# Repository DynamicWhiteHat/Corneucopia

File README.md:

# Corneucopia
A Corne based custom low-profile keyboard 

---

Corneucopia is a 42-key low profile wireless keyboard that runs on ZMK firmware. Featuring 2 OLED displays and powered by a Supermini NRF52840, this keyboard is meant to last as your daily driver. 

# Features
- 42 keys
- Per key RGB
- 2x Nice!View
- 2x Supermini NRF52840 (Nice!Nano clone)
- Hotswap sockets
- Low profile choc switches

# Why I Made This
I was initally wary of split or ergonomic keyboards as I thought they looked bad. However, while I was designing my own regular keyboard, I came across split ergo keyboards online that caught my eye, especially [this](https://www.etsy.com/listing/1337908749/ready-to-use-crkbd-corne-keyboard-v301) one. I slowly came to appreciate the look and layout of Corne keyboards, so I decided to make one. This project was a test of my PCB and CAD design skills, as well as a test of my ability to learn new things (ergogen). Overall, I think this came out very well.

# Pictures
## CAD

## PCB

## Schematic

# BOM
Note: 
- Typeractive was sometimes cheaper than AliExpress, thus some parts were sourced from them instead.
- Keycaps will be 3D printed

| Part                | Quantity      | Price   | Link                                                                                                                                                                                                                                                                                                                                                                                                                                                                                                                                      |
|---------------------|---------------|---------|-------------------------------------------------------------------------------------------------------------------------------------------------------------------------------------------------------------------------------------------------------------------------------------------------------------------------------------------------------------------------------------------------------------------------------------------------------------------------------------------------------------------------------------------|
| Kailh Hotswaps      |            70 |   $4.30 | https://www.aliexpress.us/item/3256807045726008.html?spm=a2g0o.productlist.main.6.626d50b5izCjus&algo_pvid=53812c83-dfd7-4376-8f8e-c34f3db6f02e&algo_exp_id=53812c83-dfd7-4376-8f8e-c34f3db6f02e-5&pdp_ext_f=%7B%22order%22%3A%22708%22%2C%22eval%22%3A%221%22%7D&pdp_npi=4%40dis%21USD%218.49%213.91%21%21%2160.92%2128.02%21%402103244b17542247069335737e297b%2112000039893759775%21sea%21US%216238534509%21X&curPageLogUid=VnLZ55itI6I3&utparam-url=scene%3Asearch%7Cquery_from%3A                                                     |
| Choc Switches       | 1 Pack of 70  |  $33.29 | https://www.amazon.com/Mechanical-Keyboard-switches-Chocolate-Pro-70Pcs/dp/B0DDCBL4KJ/ref=sr_1_3?crid=32V01OVDG0FH6&dib=eyJ2IjoiMSJ9.fxBe5Z4GEMZJbyuF_eaa4d6xI5EsW9uxe8cNgFLYw9cyOJJo5evMOuEAVRduMsGcHGBmw3MapZWf-BWJmWWDj5YY16v4twxpLxE8v6OxY93s_vstH-ICQffONlwd1cMobpg0_pCQesoQGqMTI_Z54wqwIzkdmZYqtPJTFfRFv11-gn-8LCyKCC6uGZ-SY1KXOGvvkI4U1F0dRwDqiQvPOQNUksX0ZSc9md0I7E6eDgI.r2LF0urYCczODaFRTe6UtlDuNLtg5oKRx1Cg0aavuK4&dib_tag=se&keywords=kailh%2Bchoc%2Bred%2Bpro&qid=1754222624&sprefix=choc%2Bpro%2Bred%2Caps%2C268&sr=8-3&th=1 |
| 1N4148 Diodes       | 1 Pack of 100 |   $1.40 | https://www.aliexpress.us/item/3256806137153769.html?spm=a2g0o.productlist.main.1.145669f2x3hJ9l&algo_pvid=26801ca0-fa57-43dc-bef8-9addec3b9d2b&algo_exp_id=26801ca0-fa57-43dc-bef8-9addec3b9d2b-0&pdp_ext_f=%7B%22order%22%3A%22395%22%2C%22eval%22%3A%221%22%7D&pdp_npi=4%40dis%21USD%211.40%211.40%21%21%2110.01%2110.01%21%40210312d517540153367636770eae10%2112000041342157154%21sea%21US%216238534509%21X&curPageLogUid=Ny6g9i4BYw4L&utparam-url=scene%3Asearch%7Cquery_from%3A                                                     |
| Nice!View           |             2 |  $40.00 | https://typeractive.xyz/products/nice-view                                                                                                                                                                                                                                                                                                                                                                                                                                                                                                |
| Supermini NRF52840  |             2 |   $5.77 | https://www.aliexpress.us/item/3256807552571798.html?gatewayAdapt=glo2usa4itemAdapt#nav-description                                                                                                                                                                                                                                                                                                                                                                                                                                       |
| Reset Button        | 1 Pack of 2   |   $1.50 | https://typeractive.xyz/products/reset-button                                                                                                                                                                                                                                                                                                                                                                                                                                                                                             |
| Power Switch        | 1 Pack of 2   |   $1.50 | https://typeractive.xyz/products/power-switch                                                                                                                                                                                                                                                                                                                                                                                                                                                                                             |
| Mill Max            |             2 |     $13 | https://typeractive.xyz/products/machine-sockets-and-pins                                                                                                                                                                                                                                                                                                                                                                                                                                                                                 |
| 110 mAh Battery     |             2 |      $8 | https://typeractive.xyz/products/lithium-battery-110mah                                                                                                                                                                                                                                                                                                                                                                                                                                                                                   |
| 2 Pin JST Connector |             1 |      $1 | https://typeractive.xyz/products/battery-jack                                                                                                                                                                                                                                                                                                                                                                                                                                                                                             |
| M2 Screws           | 1 Pack of 50  |   $1.39 | https://www.aliexpress.us/item/3256804883804669.html?spm=a2g0o.productlist.main.3.676d4a04puFjcK&algo_pvid=5e3e1c98-a0c4-41b2-8421-3b391eda04d1&algo_exp_id=5e3e1c98-a0c4-41b2-8421-3b391eda04d1-2&pdp_ext_f=%7B%22order%22%3A%228174%22%2C%22eval%22%3A%221%22%7D&pdp_npi=4%40dis%21USD%211.39%211.39%21%21%211.39%211.39%21%402103146f17540168510077312e23ad%2112000031519353259%21sea%21US%216238534509%21X&curPageLogUid=0PSBLs6x4RdT&utparam-url=scene%3Asearch%7Cquery_from%3A                                                      |
| PCB                 |             1 |  $29.85 | JLCPCB Quote                                                                                                                                                                                                                                                                                                                                                                                                                                                                                                                              |
| SK6812 Mini E LED   | 1 Pack of 100 |      $3 | https://www.aliexpress.us/item/3256802678755423.html?spm=a2g0o.productlist.main.2.27821d099KdCZl&algo_pvid=7249bb9b-f5c3-48bb-bc3a-09065b37749b&algo_exp_id=7249bb9b-f5c3-48bb-bc3a-09065b37749b-1&pdp_ext_f=%7B%22order%22%3A%2241%22%2C%22eval%22%3A%221%22%7D&pdp_npi=4%40dis%21USD%213.00%213.00%21%21%213.00%213.00%21%402103244617540165427321188e4179%2112000047195883401%21sea%21US%216238534509%21X&curPageLogUid=4d6uXghCzMX0&utparam-url=scene%3Asearch%7Cquery_from%3A                                                        |
| Acrylic Sheet       |             1 |      $6 | https://www.aliexpress.us/item/3256805181326548.html?spm=a2g0o.productlist.main.2.5cf532dcuTgGyL&algo_pvid=d63ddc6f-f83b-4167-8278-58e0f554d458&algo_exp_id=d63ddc6f-f83b-4167-8278-58e0f554d458-1&pdp_ext_f=%7B%22order%22%3A%2291%22%2C%22eval%22%3A%221%22%7D&pdp_npi=6%40dis%21USD%215.59%215.59%21%21%215.59%215.59%21%402103010e17547508573393302ec876%2112000032764729173%21sea%21US%216238534509%21X%211%210%21n_tag%3A-29912%3Bm03_new_user%3A-29895&curPageLogUid=NKCBaqv2ZbsG&utparam-url=scene%3Asearch%7Cquery_from%3A       |
| Total               |               | $149.59 |                                                                                                                                                                                                                                                                                                                                                                                                                                                                                                                                           |

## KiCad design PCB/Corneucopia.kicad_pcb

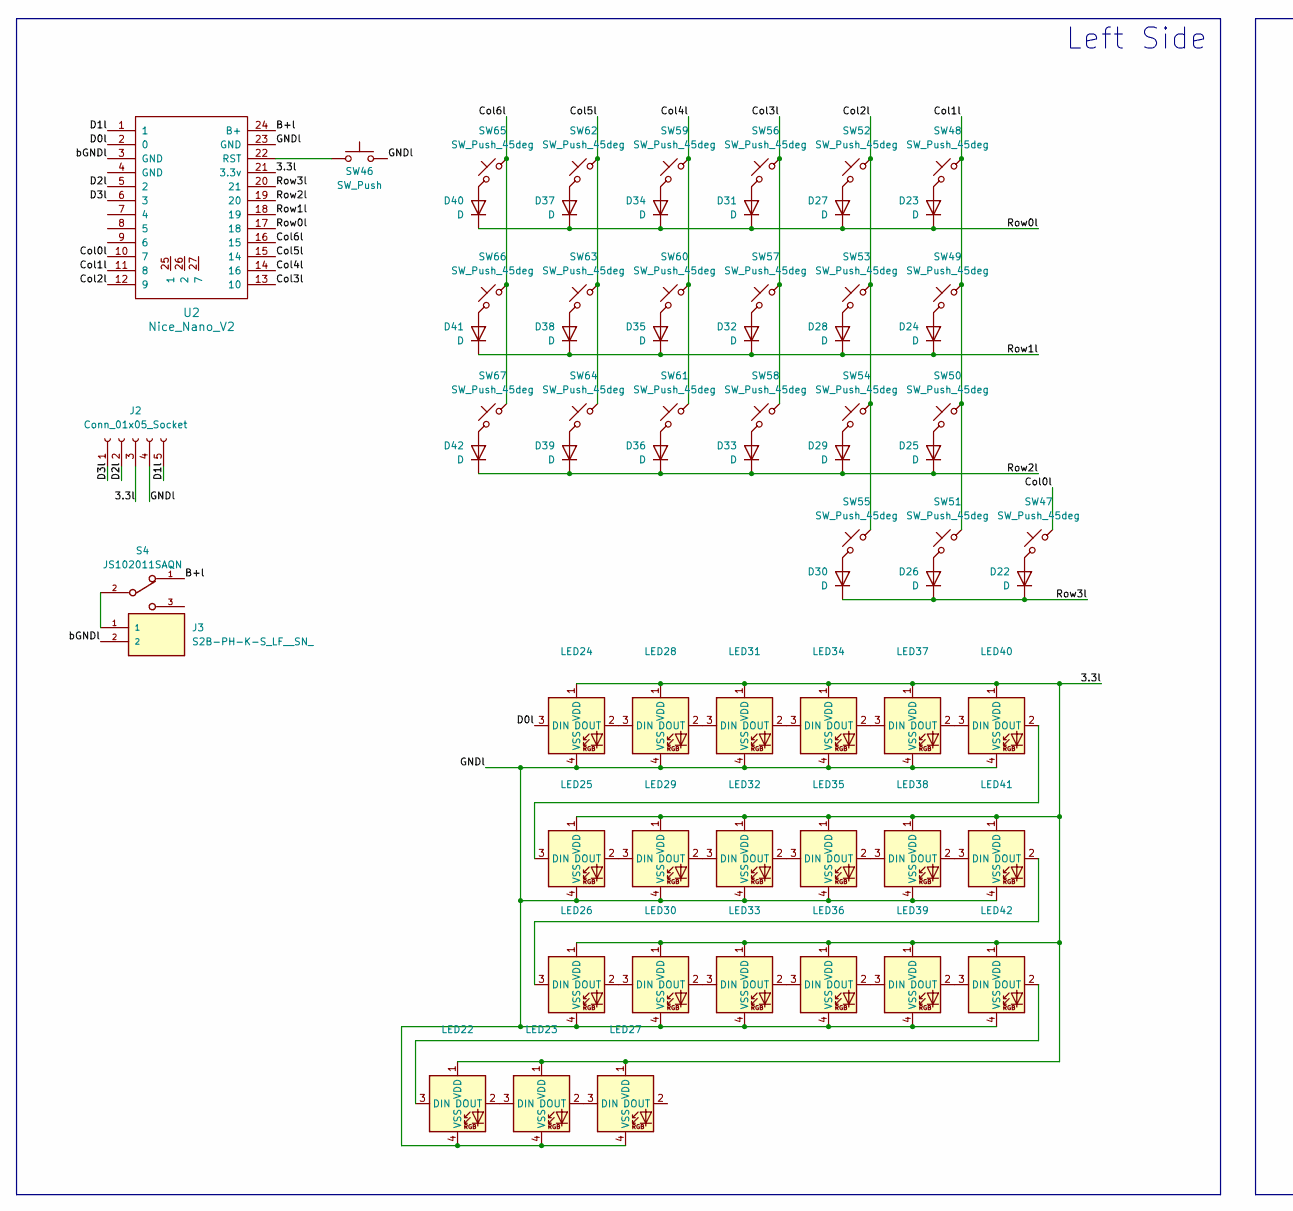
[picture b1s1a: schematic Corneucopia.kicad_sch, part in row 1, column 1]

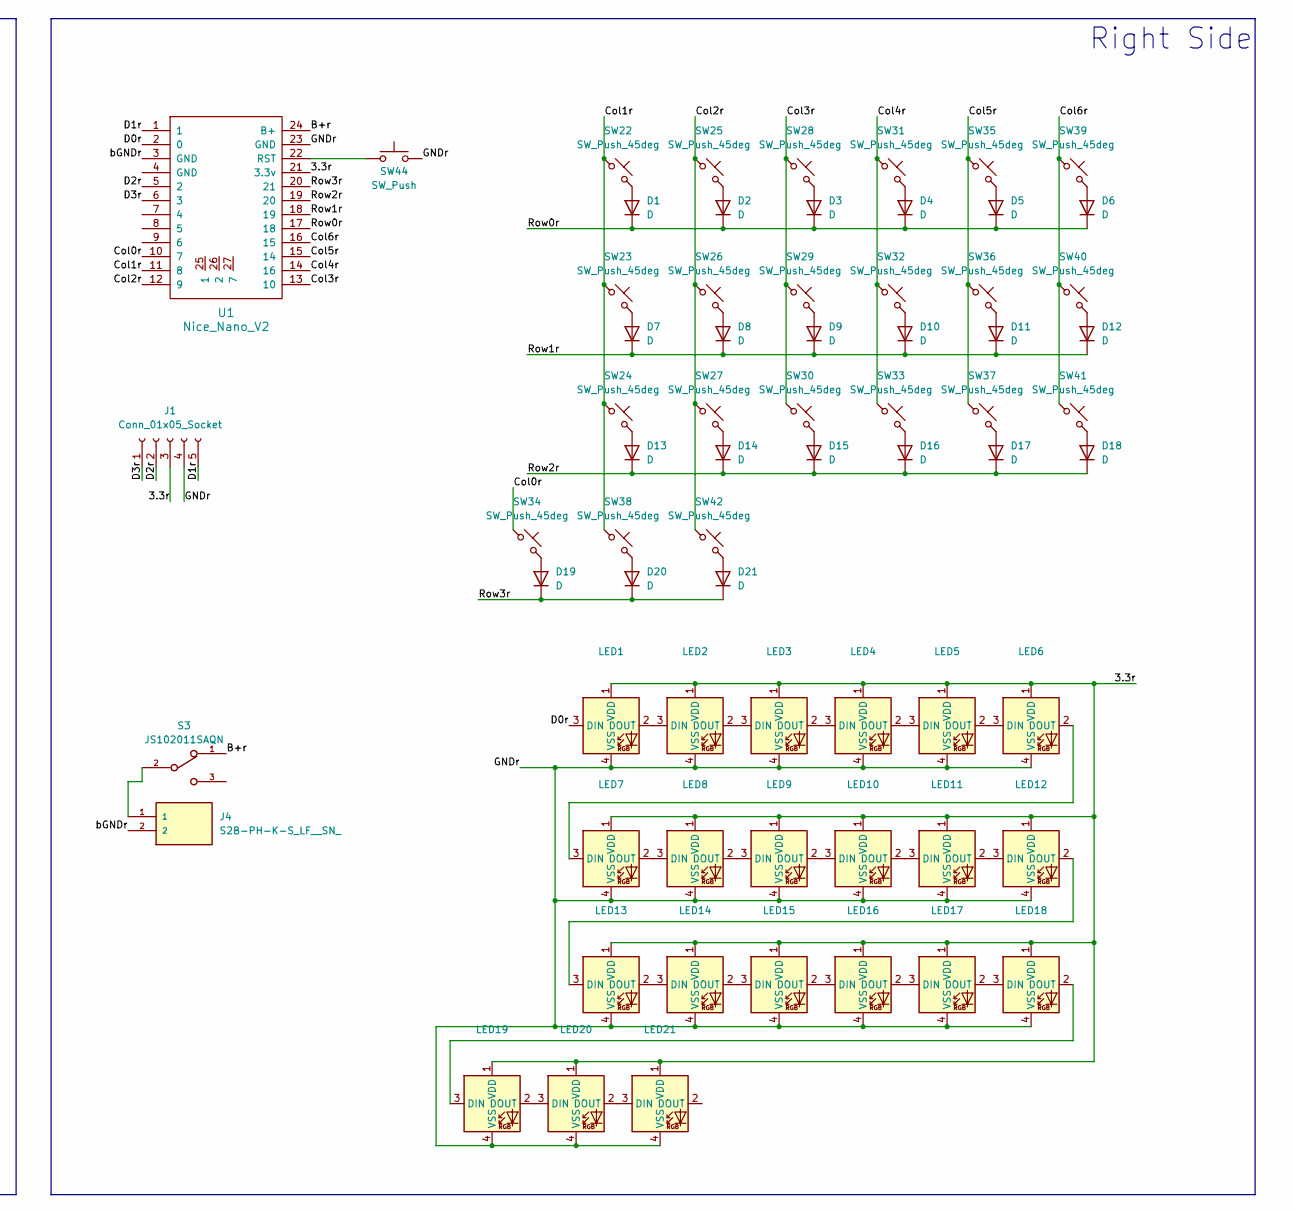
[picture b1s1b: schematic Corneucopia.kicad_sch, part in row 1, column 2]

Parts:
D1, D2, D3, D4, D5, D6, D7, D8, D9, D10, D11, D12, D13, D14, D15, D16, D17, D18, D19, D20, D21, D22, D23, D24, D25, D26, D27, D28, D29, D30, D31, D32, D33, D34, D35, D36, D37, D38, D39, D40, D41, D42: D; D_SOD-123
J1, J2: Conn_01x05_Socket; PinSocket_1x05_P2.54mm_Vertical
J3, J4: S2B-PH-K-S_LF__SN_; JST_S2B-PH-K-S_LF__SN_
LED1, LED2, LED3, LED4, LED5, LED6, LED7, LED8, LED9, LED10, LED11, LED12, LED13, LED14, LED15, LED16, LED17, LED18, LED19, LED20, LED21, LED22, LED23, LED24, LED25, LED26, LED27, LED28, LED29, LED30, LED31, LED32, LED33, LED34, LED35, LED36, LED37, LED38, LED39, LED40, LED41, LED42: choc_SK6812MINI-E; LED_choc_6028R
S3, S4: JS102011SAQN; SW_SSSS811101
SW22, SW23, SW24, SW25, SW26, SW27, SW28, SW29, SW30, SW31, SW32, SW33, SW35, SW36, SW37, SW38, SW39, SW40, SW41, SW42, SW48, SW49, SW50, SW51, SW52, SW53, SW54, SW55, SW56, SW57, SW58, SW59, SW60, SW61, SW62, SW63, SW64, SW65, SW66, SW67: SW_Push_45deg; choc_3D_hotswap
SW34, SW47: SW_Push_45deg; SW_choc_v1_HS_CPG135001S30_1.5u
SW44, SW46: SW_Push; SW_EVQPUJ_4P7X3P5_PAN
U1, U2: Nice_Nano_V2; nice_nano_H_USBdn

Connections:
/3.3l: J2.3, LED22.1 (VDD), LED23.1 (VDD), LED24.1 (VDD), LED25.1 (VDD), LED26.1 (VDD), LED27.1 (VDD), LED28.1 (VDD), LED29.1 (VDD), LED30.1 (VDD), LED31.1 (VDD), LED32.1 (VDD), LED33.1 (VDD), LED34.1 (VDD), LED35.1 (VDD), LED36.1 (VDD), LED37.1 (VDD), LED38.1 (VDD), LED39.1 (VDD), LED40.1 (VDD), LED41.1 (VDD), LED42.1 (VDD), U2.21 (3.3v)
/3.3r: J1.3, LED1.1 (VDD), LED2.1 (VDD), LED3.1 (VDD), LED4.1 (VDD), LED5.1 (VDD), LED6.1 (VDD), LED7.1 (VDD), LED8.1 (VDD), LED9.1 (VDD), LED10.1 (VDD), LED11.1 (VDD), LED12.1 (VDD), LED13.1 (VDD), LED14.1 (VDD), LED15.1 (VDD), LED16.1 (VDD), LED17.1 (VDD), LED18.1 (VDD), LED19.1 (VDD), LED20.1 (VDD), LED21.1 (VDD), U1.21 (3.3v)
/B+l: S4.1, U2.24 (B+)
/B+r: S3.1, U1.24 (B+)
/Col0l: SW47.1, U2.10 (7)
/Col0r: SW34.1, U1.10 (7)
/Col1l: SW48.1, SW49.1, SW50.1, SW51.1, U2.11 (8)
/Col1r: SW22.1, SW23.1, SW24.1, SW38.1, U1.11 (8)
/Col2l: SW52.1, SW53.1, SW54.1, SW55.1, U2.12 (9)
/Col2r: SW25.1, SW26.1, SW27.1, SW42.1, U1.12 (9)
/Col3l: SW56.1, SW57.1, SW58.1, U2.13 (10)
/Col3r: SW28.1, SW29.1, SW30.1, U1.13 (10)
/Col4l: SW59.1, SW60.1, SW61.1, U2.14 (16)
/Col4r: SW31.1, SW32.1, SW33.1, U1.14 (16)
/Col5l: SW62.1, SW63.1, SW64.1, U2.15 (14)
/Col5r: SW35.1, SW36.1, SW37.1, U1.15 (14)
/Col6l: SW65.1, SW66.1, SW67.1, U2.16 (15)
/Col6r: SW39.1, SW40.1, SW41.1, U1.16 (15)
/D0l: LED24.3 (DIN), U2.2 (0)
/D0r: LED1.3 (DIN), U1.2 (0)
/D1l: J2.5, U2.1
/D1r: J1.5, U1.1
/D2l: J2.2, U2.5 (2)
/D2r: J1.2, U1.5 (2)
/D3l: J2.1, U2.6 (3)
/D3r: J1.1, U1.6 (3)
/GNDl: J2.4, LED22.4 (VSS), LED23.4 (VSS), LED24.4 (VSS), LED25.4 (VSS), LED26.4 (VSS), LED27.4 (VSS), LED28.4 (VSS), LED29.4 (VSS), LED30.4 (VSS), LED31.4 (VSS), LED32.4 (VSS), LED33.4 (VSS), LED34.4 (VSS), LED35.4 (VSS), LED36.4 (VSS), LED37.4 (VSS), LED38.4 (VSS), LED39.4 (VSS), LED40.4 (VSS), LED41.4 (VSS), LED42.4 (VSS), SW46.2, U2.23 (GND)
/GNDr: J1.4, LED1.4 (VSS), LED2.4 (VSS), LED3.4 (VSS), LED4.4 (VSS), LED5.4 (VSS), LED6.4 (VSS), LED7.4 (VSS), LED8.4 (VSS), LED9.4 (VSS), LED10.4 (VSS), LED11.4 (VSS), LED12.4 (VSS), LED13.4 (VSS), LED14.4 (VSS), LED15.4 (VSS), LED16.4 (VSS), LED17.4 (VSS), LED18.4 (VSS), LED19.4 (VSS), LED20.4 (VSS), LED21.4 (VSS), SW44.2, U1.23 (GND)
/Row0l: D23.1 (K), D27.1 (K), D31.1 (K), D34.1 (K), D37.1 (K), D40.1 (K), U2.17 (18)
/Row0r: D1.1 (K), D2.1 (K), D3.1 (K), D4.1 (K), D5.1 (K), D6.1 (K), U1.17 (18)
/Row1l: D24.1 (K), D28.1 (K), D32.1 (K), D35.1 (K), D38.1 (K), D41.1 (K), U2.18 (19)
/Row1r: D7.1 (K), D8.1 (K), D9.1 (K), D10.1 (K), D11.1 (K), D12.1 (K), U1.18 (19)
/Row2l: D25.1 (K), D29.1 (K), D33.1 (K), D36.1 (K), D39.1 (K), D42.1 (K), U2.19 (20)
/Row2r: D13.1 (K), D14.1 (K), D15.1 (K), D16.1 (K), D17.1 (K), D18.1 (K), U1.19 (20)
/Row3l: D22.1 (K), D26.1 (K), D30.1 (K), U2.20 (21)
/Row3r: D19.1 (K), D20.1 (K), D21.1 (K), U1.20 (21)
/bGNDl: J3.2, U2.3 (GND)
/bGNDr: J4.2, U1.3 (GND)
unnamed: D1.2 (A), SW22.2
unnamed: D2.2 (A), SW25.2
unnamed: D3.2 (A), SW28.2
unnamed: D4.2 (A), SW31.2
unnamed: D5.2 (A), SW35.2
unnamed: D6.2 (A), SW39.2
unnamed: D7.2 (A), SW23.2
unnamed: D8.2 (A), SW26.2
unnamed: D9.2 (A), SW29.2
unnamed: D10.2 (A), SW32.2
unnamed: D11.2 (A), SW36.2
unnamed: D12.2 (A), SW40.2
unnamed: D13.2 (A), SW24.2
unnamed: D14.2 (A), SW27.2
unnamed: D15.2 (A), SW30.2
unnamed: D16.2 (A), SW33.2
unnamed: D17.2 (A), SW37.2
unnamed: D18.2 (A), SW41.2
unnamed: D19.2 (A), SW34.2
unnamed: D20.2 (A), SW38.2
unnamed: D21.2 (A), SW42.2
unnamed: D22.2 (A), SW47.2
unnamed: D23.2 (A), SW48.2
unnamed: D24.2 (A), SW49.2
unnamed: D25.2 (A), SW50.2
unnamed: D26.2 (A), SW51.2
unnamed: D27.2 (A), SW52.2
unnamed: D28.2 (A), SW53.2
unnamed: D29.2 (A), SW54.2
unnamed: D30.2 (A), SW55.2
unnamed: D31.2 (A), SW56.2
unnamed: D32.2 (A), SW57.2
unnamed: D33.2 (A), SW58.2
unnamed: D34.2 (A), SW59.2
unnamed: D35.2 (A), SW60.2
unnamed: D36.2 (A), SW61.2
unnamed: D37.2 (A), SW62.2
unnamed: D38.2 (A), SW63.2
unnamed: D39.2 (A), SW64.2
unnamed: D40.2 (A), SW65.2
unnamed: D41.2 (A), SW66.2
unnamed: D42.2 (A), SW67.2
unnamed: J3.1, S4.2
unnamed: J4.1, S3.2
unnamed: LED1.2 (DOUT), LED2.3 (DIN)
unnamed: LED2.2 (DOUT), LED3.3 (DIN)
unnamed: LED3.2 (DOUT), LED4.3 (DIN)
unnamed: LED4.2 (DOUT), LED5.3 (DIN)
unnamed: LED5.2 (DOUT), LED6.3 (DIN)
unnamed: LED6.2 (DOUT), LED7.3 (DIN)
unnamed: LED7.2 (DOUT), LED8.3 (DIN)
unnamed: LED8.2 (DOUT), LED9.3 (DIN)
unnamed: LED9.2 (DOUT), LED10.3 (DIN)
unnamed: LED10.2 (DOUT), LED11.3 (DIN)
unnamed: LED11.2 (DOUT), LED12.3 (DIN)
unnamed: LED12.2 (DOUT), LED13.3 (DIN)
unnamed: LED13.2 (DOUT), LED14.3 (DIN)
unnamed: LED14.2 (DOUT), LED15.3 (DIN)
unnamed: LED15.2 (DOUT), LED16.3 (DIN)
unnamed: LED16.2 (DOUT), LED17.3 (DIN)
unnamed: LED17.2 (DOUT), LED18.3 (DIN)
unnamed: LED18.2 (DOUT), LED19.3 (DIN)
unnamed: LED19.2 (DOUT), LED20.3 (DIN)
unnamed: LED20.2 (DOUT), LED21.3 (DIN)
unnamed: LED22.3 (DIN), LED42.2 (DOUT)
unnamed: LED22.2 (DOUT), LED23.3 (DIN)
unnamed: LED23.2 (DOUT), LED27.3 (DIN)
unnamed: LED24.2 (DOUT), LED28.3 (DIN)
unnamed: LED25.3 (DIN), LED40.2 (DOUT)
unnamed: LED25.2 (DOUT), LED29.3 (DIN)
unnamed: LED26.3 (DIN), LED41.2 (DOUT)
unnamed: LED26.2 (DOUT), LED30.3 (DIN)
unnamed: LED28.2 (DOUT), LED31.3 (DIN)
unnamed: LED29.2 (DOUT), LED32.3 (DIN)
unnamed: LED30.2 (DOUT), LED33.3 (DIN)
unnamed: LED31.2 (DOUT), LED34.3 (DIN)
unnamed: LED32.2 (DOUT), LED35.3 (DIN)
unnamed: LED33.2 (DOUT), LED36.3 (DIN)
unnamed: LED34.2 (DOUT), LED37.3 (DIN)
unnamed: LED35.2 (DOUT), LED38.3 (DIN)
unnamed: LED36.2 (DOUT), LED39.3 (DIN)
unnamed: LED37.2 (DOUT), LED40.3 (DIN)
unnamed: LED38.2 (DOUT), LED41.3 (DIN)
unnamed: LED39.2 (DOUT), LED42.3 (DIN)
unnamed: SW44.1, U1.22 (RST)
unnamed: SW46.1, U2.22 (RST)

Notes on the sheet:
Right Side
Left Side

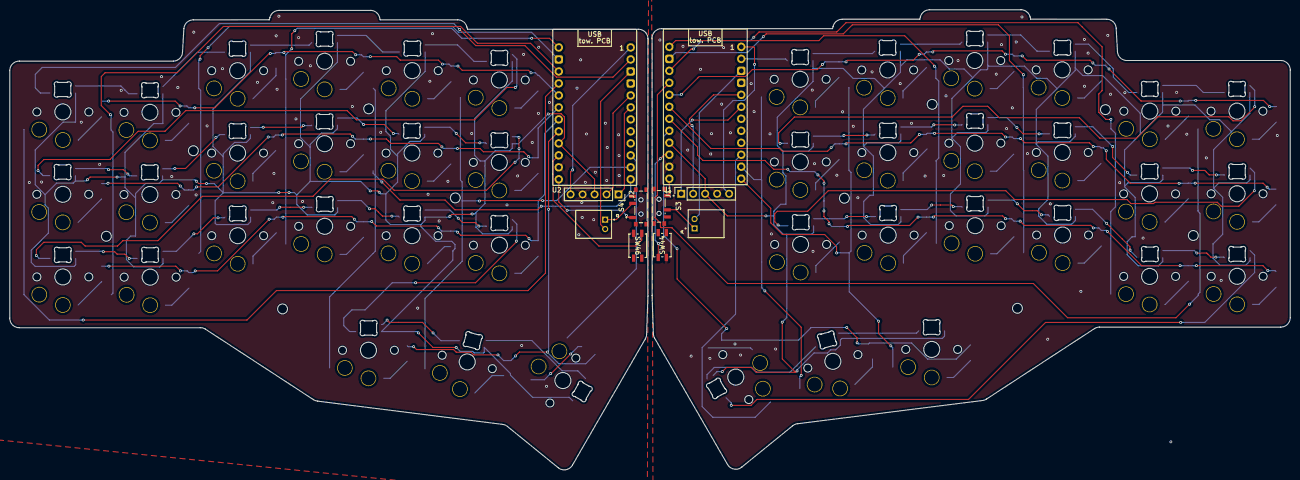
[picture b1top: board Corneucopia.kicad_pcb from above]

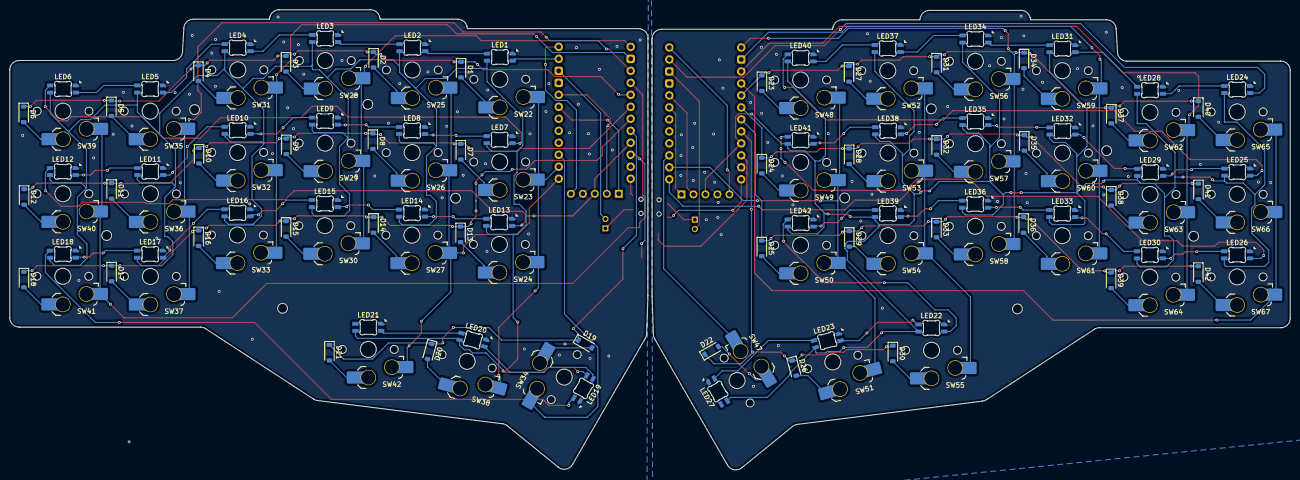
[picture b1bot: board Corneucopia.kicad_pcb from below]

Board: 2 copper layers, 271.4 x 97.5 mm, 146 parts (126 on the bottom side), 124 nets.

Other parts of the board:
H1, H1#2, H1#3, H1#4, H1#5, H1#6, H1#7, H2, H3, H4: MountingHole_2.1mm

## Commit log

2025-08-01 Added files
